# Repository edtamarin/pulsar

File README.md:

# pulsar
Line Follower robot for the 2017 RobotChallenge.

## Hardware
### Chassis
The body of the robot is a custom-made PCB. In hindsight, this added more weight to the overall design. The PCB was designed in EagleCAD.
### Wheels
To increase traction, the wheels were custom-made. The rims were 3D printed to be wide for more grip. The tyres were made from a silicone tube to increase grip on the surface.

## Code
The code is very simple. This design does not use a PID, however it would benefit from one. 

The array of sensors was placed in the front of the robot. The algorithm calculates the deviation from the straight line and runs the motors accordingly.

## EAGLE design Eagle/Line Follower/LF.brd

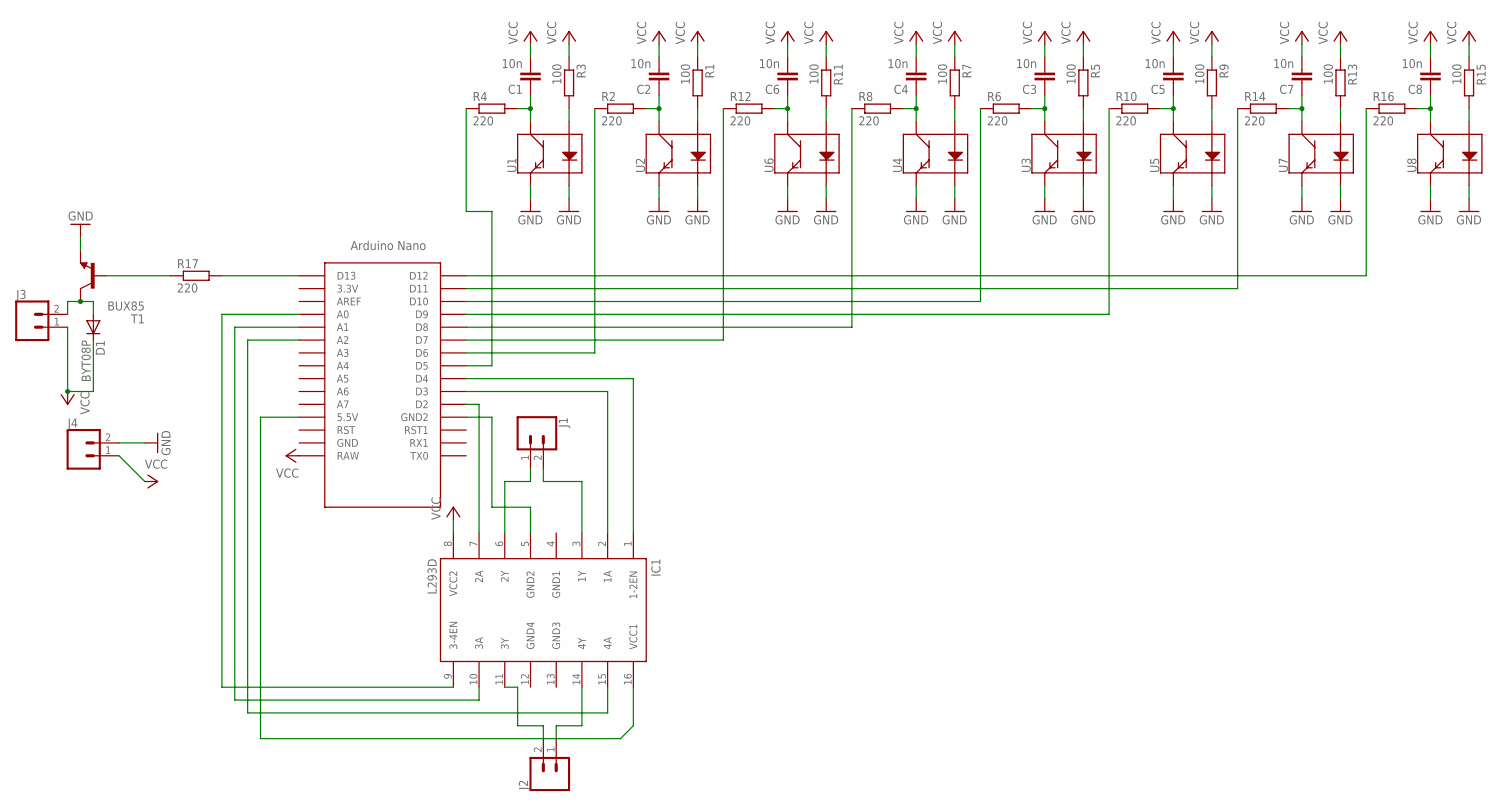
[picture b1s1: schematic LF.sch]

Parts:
C1, C2, C3, C4, C5, C6, C7, C8: 10n; C0402
D1: BYT08P; TO220ACS
IC1: L293D; DIL16
J1, J2, J3, J4: CONN_02; 1X02
R1, R3, R5, R7, R9, R11, R13, R15: 100; R0402
R2, R4, R6, R8, R10, R12, R14, R16: 220; R0402
R17: 220; R1206
T1: BUX85; TO220
U1, U2, U3, U4, U5, U6, U7, U8: QRE1113SMD-W; QRE1113-W
U$1: NANO

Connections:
GND: J4.2, T1.3 (E), U1.2 (K), U1.4 (E), U2.2 (K), U2.4 (E), U3.2 (K), U3.4 (E), U4.2 (K), U4.4 (E), U5.2 (K), U5.4 (E), U6.2 (K), U6.4 (E), U7.2 (K), U7.4 (E), U8.2 (K), U8.4 (E)
GND1: IC1.4 (GND1)
GND3: IC1.13 (GND3)
GND4: IC1.12 (GND4)
unnamed: R3.2, U1.1 (A)
unnamed: C1.1, R4.2, U1.3 (C)
unnamed: R16.1, U$1.D12
unnamed: R1.2, U2.1 (A)
unnamed: C2.1, R2.2, U2.3 (C)
unnamed: R5.2, U3.1 (A)
unnamed: C3.1, R6.2, U3.3 (C)
unnamed: R7.2, U4.1 (A)
unnamed: C4.1, R8.2, U4.3 (C)
unnamed: R9.2, U5.1 (A)
unnamed: C5.1, R10.2, U5.3 (C)
unnamed: R11.2, U6.1 (A)
unnamed: C6.1, R12.2, U6.3 (C)
unnamed: R13.2, U7.1 (A)
unnamed: C7.1, R14.2, U7.3 (C)
unnamed: R15.2, U8.1 (A)
unnamed: C8.1, R16.2, U8.3 (C)
unnamed: R14.1, U$1.D11
unnamed: R6.1, U$1.D10
unnamed: R10.1, U$1.D9
unnamed: R8.1, U$1.D8
unnamed: R12.1, U$1.D7
unnamed: R2.1, U$1.D6
unnamed: R4.1, U$1.D5
unnamed: IC1.1 (1-2EN), U$1.D4
unnamed: IC1.2 (1A), U$1.D3
unnamed: IC1.7 (2A), U$1.D2
unnamed: IC1.9 (3-4EN), U$1.A0
unnamed: IC1.10 (3A), U$1.A1
unnamed: IC1.15 (4A), U$1.A2
unnamed: IC1.6 (2Y), J1.1
unnamed: IC1.3 (1Y), J1.2
unnamed: IC1.5 (GND2), U$1.GND1 (GND2)
unnamed: IC1.11 (3Y), J2.2
unnamed: IC1.14 (4Y), J2.1
unnamed: IC1.16 (VCC1), U$1.5V (5.5V)
unnamed: R17.2, U$1.D13
unnamed: R17.1, T1.1 (B)
unnamed: D1.A, J3.2, T1.2 (C)
VCC: C1.2, C2.2, C3.2, C4.2, C5.2, C6.2, C7.2, C8.2, D1.C, IC1.8 (VCC2), J3.1, J4.1, R1.1, R3.1, R5.1, R7.1, R9.1, R11.1, R13.1, R15.1, U$1.RAW

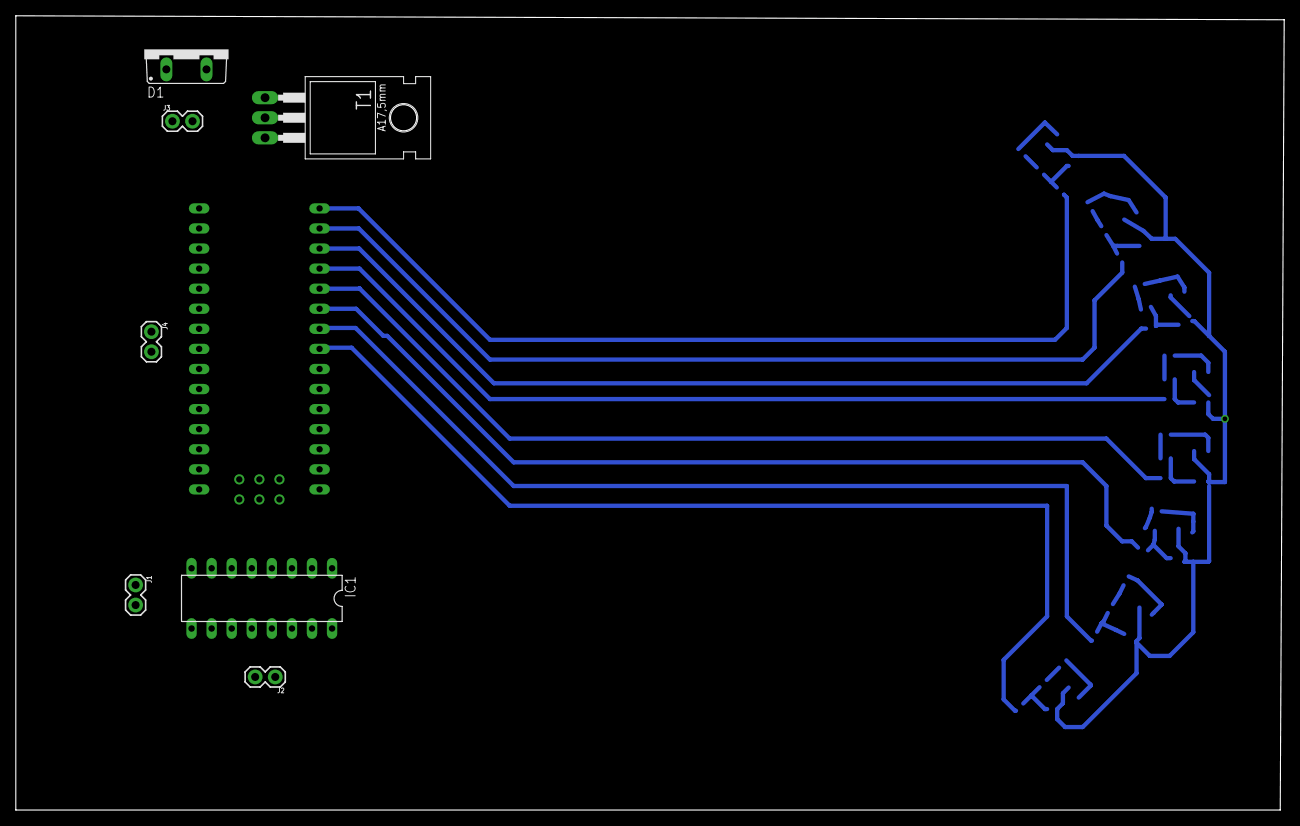
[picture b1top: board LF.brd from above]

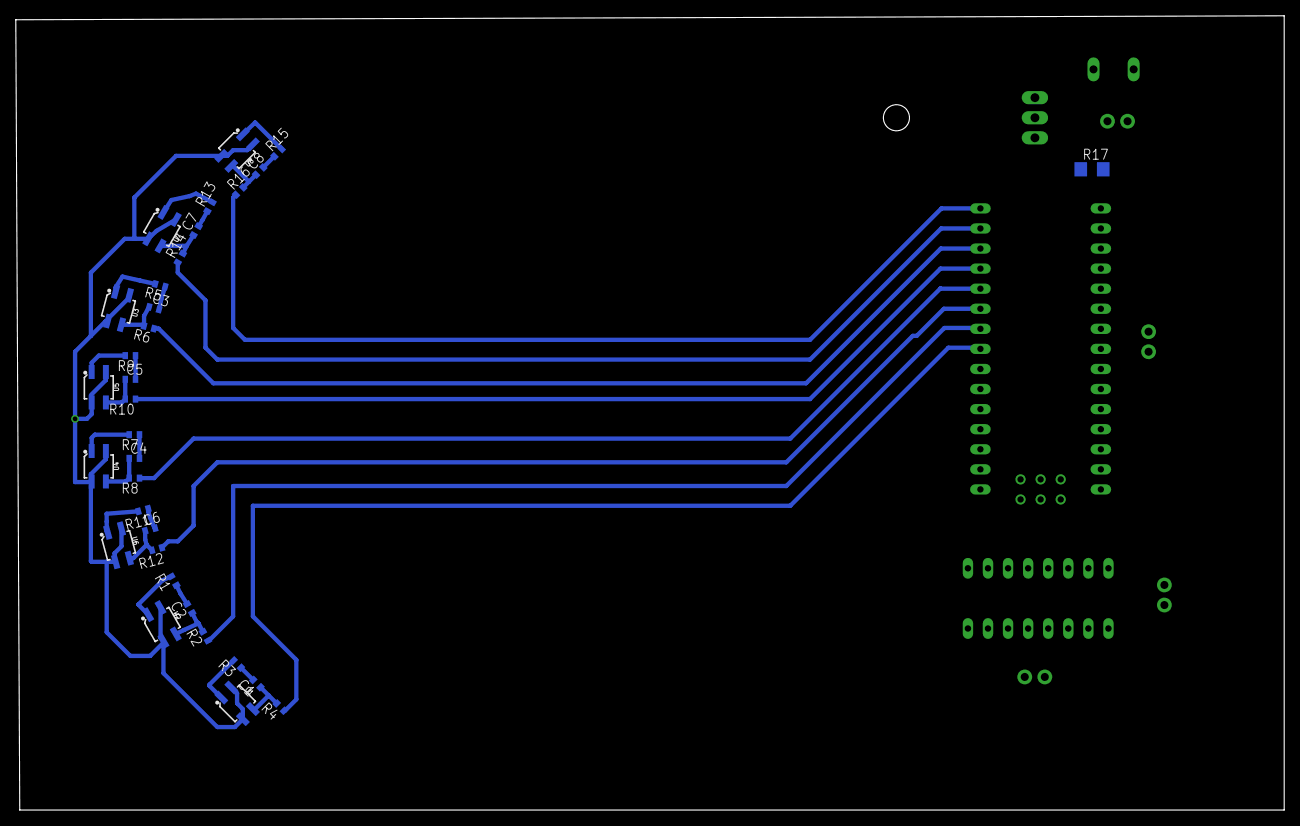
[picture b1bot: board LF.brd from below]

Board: 2 copper layers, 160.5 x 100.5 mm, 41 parts (33 on the bottom side), 41 nets.

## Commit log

2020-08-20 Added the full project to GitHub

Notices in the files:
parts and their libraries:
SparkFun-Connectors: Licensing: Creative Commons ShareAlike 4.0 International - https://creativecommons.org/licenses/by-sa/4.0
